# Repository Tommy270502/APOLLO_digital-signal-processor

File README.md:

# APOLLO Digital Signal Processor

APOLLO is a USB-powered STM32F401 digital signal-processing board and firmware
case study. The repository combines KiCad hardware design, STM32CubeIDE
firmware, external analog and memory devices, host-side tests for reusable C
logic, and validation notes for hardware-dependent behavior.

## What This Demonstrates

- STM32F401 firmware architecture with CubeMX-generated code kept separate from
  hand-written application logic.
- USB CDC command and telemetry interface for live DSP configuration.
- Two-channel analog input support, external I2C DAC output, and SPI SRAM
  circular sample logging.
- Embedded-friendly DSP filters with fixed buffers and parameter validation.
- Clear distinction between implemented, host-tested, and hardware-validation
  required features.

## System Overview

```mermaid
flowchart LR
    Host["PC serial monitor"] <-- "USB CDC" --> USB["USB-C + ESD"]
    USB --> MCU["STM32F401RBTx\n84 MHz Cortex-M4F"]
    AIN["AIN0 / AIN1"] --> Analog["MCP602 analog conditioning"]
    Analog --> ADC["ADC1 CH0 / CH1"]
    ADC --> MCU
    MCU -- "I2C1 PB6/PB7" --> DAC["MCP4725-family\n12-bit I2C DAC"]
    DAC --> AOUT["Analog output"]
    MCU -- "SPI1 PA5/PA6/PA7" --> SRAM["23K256\n32 KiB SPI SRAM"]
    MCU -- "SPI1 + SD_nCS" --> SD["microSD socket\nFatFs CSV logging"]
    MCU --> SWD["SWD debug"]
    MCU --> UART["USART1 header"]
```

## Firmware Architecture

```mermaid
flowchart TD
    Main["main.c\nHAL + CubeMX init"] --> App["app/apollo_app"]
    App --> ADC["platform/apollo_adc\nbounded polling"]
    App --> USB["platform/apollo_usb_cdc\nRX line buffer + TX wrapper"]
    App --> Chain["app/apollo_signal_chain"]
    Chain --> DSP["dsp/dsp_filters"]
    App --> DAC["drivers/dac_driver"]
    App --> Store["app/apollo_storage"]
    Store --> SRAM["drivers/sram_23k256"]
    App --> Tel["app/apollo_telemetry"]
    App --> Diag["app/apollo_diagnostics"]
    App --> CLI["app/apollo_cli"]
```

`main.c` now performs HAL initialization, CubeMX peripheral initialization, and
then calls `apollo_app_init()` and `apollo_app_task()`. Application behavior is
kept under `Software/Apollo - DSP/Core/Inc/*` and
`Software/Apollo - DSP/Core/Src/*`.

## Signal Pipeline

```mermaid
flowchart LR
    Source{"Source"} -->|ADC CH0/CH1| Raw["raw ADC"]
    Source -->|demo mode| Raw
    Raw --> Cal["offset/gain calibration"]
    Cal --> Filter["runtime DSP filter"]
    Filter --> Clamp["DAC saturation handling"]
    Clamp --> DAC["I2C DAC write"]
    Filter --> Telemetry["USB CDC telemetry"]
    Clamp --> Log["SPI SRAM circular log"]
    Raw --> Diagnostics["min/max/mean/errors"]
```

Default firmware behavior preserves the original demo path: ADC channel 0 is
sampled, a 1 kHz first-order low-pass filter is applied, the result is written
to the external DAC, telemetry is streamed over USB CDC, and compact sample
records are written to external SRAM when the SRAM self-test passes.

## USB Commands

Commands are sent over the USB CDC virtual COM port with newline termination.

| Command | Purpose |
| --- | --- |
| `help` | Print command summary. |
| `status` | Print sample count, channel, filter, demo, calibration, storage, and error counters. |
| `filter bypass` | Disable filtering. |
| `filter lowpass <hz>` | First-order low-pass IIR. |
| `filter highpass <hz>` | First-order high-pass IIR. |
| `filter ema <alpha>` | Exponential moving average, `0 < alpha <= 1`. |
| `filter average <n>` | Moving average, up to 16 samples. |
| `filter median <n>` | Median filter, up to 9 samples. |
| `input 0` / `input 1` | Select ADC channel 0 or 1. |
| `demo off\|sine\|step\|impulse` | Use real ADC input or synthetic samples. |
| `telemetry on\|off` | Enable or disable periodic telemetry frames. |
| `calibrate clear` | Restore unity ADC/DAC scaling. |
| `calibrate adc <gain> <offset>` | Set ADC input calibration (gain 0.01-100, offset +/-4095). |
| `calibrate dac <gain> <offset>` | Set DAC output calibration (gain 0.01-100, offset +/-4095). |

## Telemetry

Sample frames use this CSV format:

```text
T,timestamp_ms,sequence,channel,raw_adc,filtered,dac_code,filter,flags
```

Example:

```text
T,1200,57,0,1820,1784.42,1784,lowpass,0x00000000
```

Flags report clipping, demo source, filter errors, ADC errors, DAC errors, and
SRAM logging errors.

## Repository Layout

| Path | Purpose |
| --- | --- |
| `Apollo - DSP.kicad_pro` | Main KiCad project. |
| `Apollo - DSP.kicad_sch`, `Analog.kicad_sch`, `DSP.kicad_sch` | Hardware schematics. |
| `Apollo - DSP.kicad_pcb` | PCB layout. |
| `Gerber/` | Fabrication outputs. |
| `pictures/` | Board images. |
| `datasheets/` | Local component datasheets. |
| `Software/Apollo - DSP/` | STM32CubeIDE firmware project. |
| `tests/host/` | Host-buildable tests for pure C logic. |
| `docs/` | Technical documentation and validation notes. |

See [REPOSITORY_STRUCTURE.md](REPOSITORY_STRUCTURE.md) for more detail.

## Build And Flash

1. Open STM32CubeIDE.
2. Import `Software/Apollo - DSP/` as an existing STM32CubeIDE project.
3. Build the Debug or Release configuration.
4. Flash/debug over the SWD header using an ST-LINK compatible probe.
5. Open the USB CDC virtual COM port with a serial terminal.
6. Send `help`, `status`, or `demo sine` to verify the command path.

Generated `Debug/` and `Release/` folders are intentionally not tracked.
STM32CubeIDE regenerates them locally.

## Host Tests

Host tests cover pure logic that does not require STM32 HAL or board hardware:

```sh
make -C tests/host test
```

The tests exercise DSP filter behavior, command parsing, telemetry formatting,
diagnostics, calibration/clipping math, and signal-chain demo paths.

## Validation Status

- Host tests pass on Windows 11 / MSYS2 / GCC 15.2.0 (2026-05-27).
- Firmware Debug and Release builds pass with 0 errors (STM32CubeIDE 2.0.0,
  arm-none-eabi-gcc 14.3.1, 2026-05-27).
- Hardware-dependent behavior requires board validation:
  ADC channel accuracy, DAC output voltage, SRAM SPI timing, and USB behavior
  under sustained traffic.
- microSD logging writes CSV through FatFs over an SPI block driver; the
  logic is covered by host tests but has not been exercised on a card yet
  until a real SPI block-device and filesystem implementation is added.

See [docs/validation.md](docs/validation.md) for the full validation checklist.

## Engineering Highlights

- CubeMX-generated code is preserved and hand-written application code is moved
  into reviewable modules.
- Peripheral failures no longer force infinite retry loops in application code.
- Runtime filter selection and demo sources make the board demonstrable without
  external analog equipment.
- Documentation states validation limits instead of claiming untested hardware
  support.

## Future Work

- Move ADC acquisition to timer-triggered DMA with overrun accounting.
- Validate microSD logging on hardware and record the observed results.
- Add fixture-based hardware tests for DAC linearity, ADC channel calibration,
  SRAM retention, and USB throughput.
- Add optional firmware CI if a reproducible STM32 toolchain image is adopted.

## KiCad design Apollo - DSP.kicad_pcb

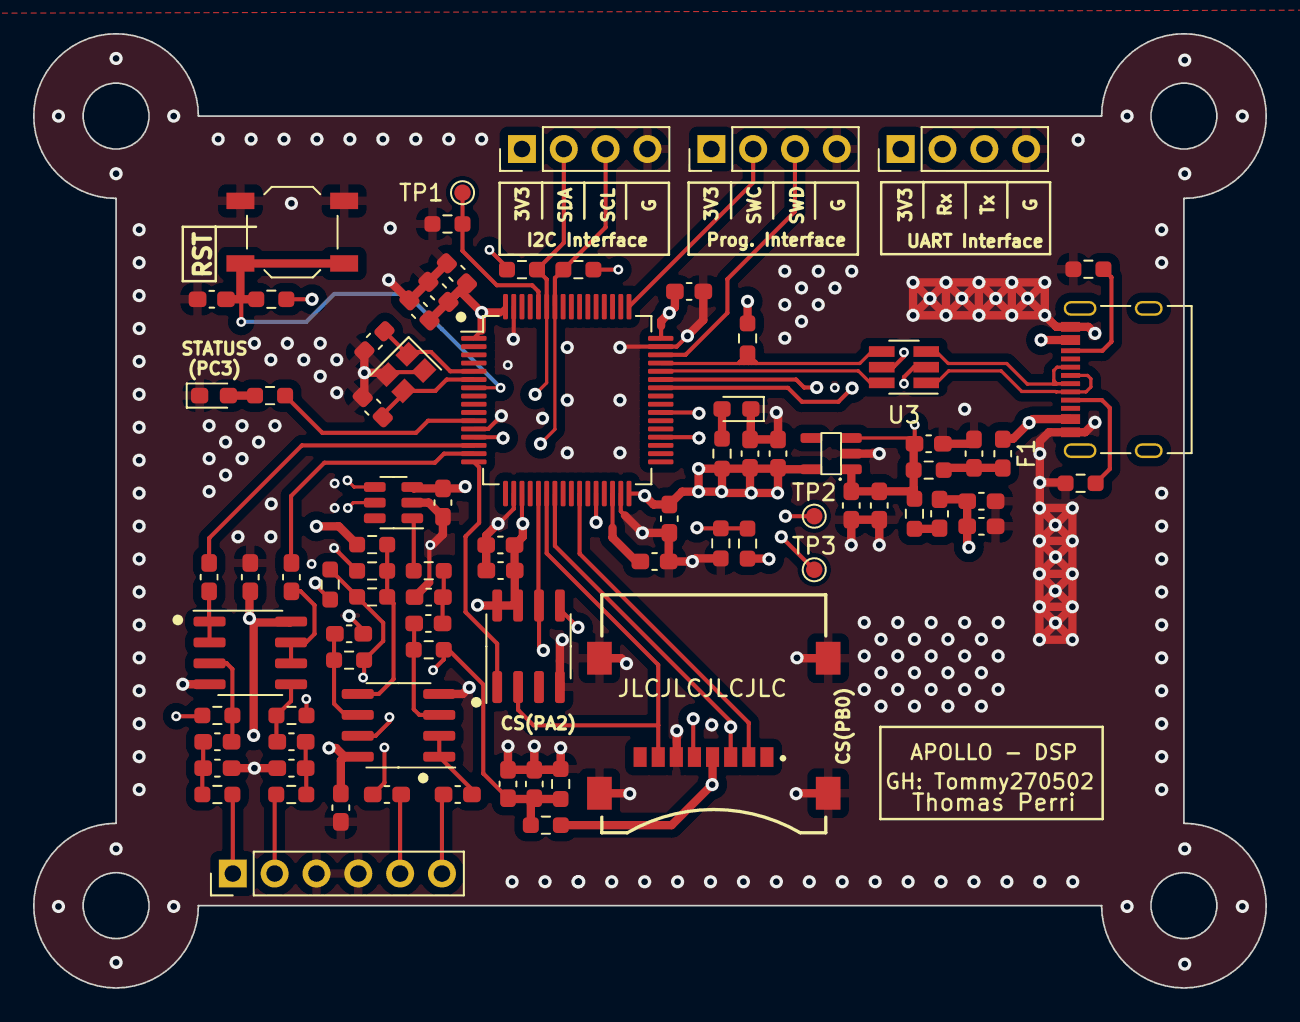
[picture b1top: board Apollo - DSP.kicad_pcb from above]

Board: 4 copper layers, 74.9 x 58.0 mm, 83 parts (0 on the bottom side), 56 nets.

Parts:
C1, C2, C3, C5, C8, C13, C14, C20, C23: 10u; C_0603_1608Metric_Pad1.08x0.95mm_HandSolder
C4, C6, C15, C16, C17, C18, C19, C21, C26, C29, C30, C31, C32, C34, C36, C37, C39, C40, C41, C42: 100n; C_0603_1608Metric_Pad1.08x0.95mm_HandSolder
C7: 220u; C_0603_1608Metric_Pad1.08x0.95mm_HandSolder
C24, C25: 10p; C_0603_1608Metric_Pad1.08x0.95mm_HandSolder
C33, C35, C38: 1n; C_0603_1608Metric_Pad1.08x0.95mm_HandSolder
D1: Red; LED_0603_1608Metric_Pad1.05x0.95mm_HandSolder
D2: Green; LED_0603_1608Metric_Pad1.05x0.95mm_HandSolder
F1: 500mA; Fuse_0603_1608Metric_Pad1.05x0.95mm_HandSolder
FB1: 100R@100MHz; R_0603_1608Metric_Pad0.98x0.95mm_HandSolder
J1: USB_C_Receptacle_USB2.0; USB_C_Receptacle_Palconn_UTC16-G
J2, J3, J6: Conn_01x04; PinHeader_1x04_P2.54mm_Vertical
J4: MEM2067-02-180-00-A_REVB; GCT_MEM2067-02-180-00-A_REVB
J5: Conn_01x06; PinHeader_1x06_P2.54mm_Vertical
L1: 8u8; L_0603_1608Metric_Pad1.05x0.95mm_HandSolder
R1, R8: 1k; R_0603_1608Metric_Pad0.98x0.95mm_HandSolder
R2, R3: 5.1k; R_0603_1608Metric_Pad0.98x0.95mm_HandSolder
R4, R5, R9, R10, R16, R18, R19, R21: 5k1; R_0603_1608Metric_Pad0.98x0.95mm_HandSolder
R6, R7, R22, R23: 10k; R_0603_1608Metric_Pad0.98x0.95mm_HandSolder
R11, R12, R15: 1M; R_0603_1608Metric_Pad0.98x0.95mm_HandSolder
R13: 1.5k; R_0603_1608Metric_Pad0.98x0.95mm_HandSolder
R13#2, R14, R17, R20: 160R; R_0603_1608Metric_Pad0.98x0.95mm_HandSolder
R24: 10R; R_0603_1608Metric_Pad0.98x0.95mm_HandSolder
RESET1: RST; SW_SPST_TL3342
TP1, TP2, TP3: TestPoint; TestPoint_Pad_D1.0mm
U1: NCP115ASN330T2G
U3: USBLC6-2SC6; SOT-23-6_Handsoldering
U4: STM32F401RBTx; LQFP-64_10x10mm_P0.5mm
U5: 23K256; SOIC-8_3.9x4.9mm_P1.27mm
U6: MCP4725xxx-xCH; SOT-23-6
U7, U8: MCP602; SOIC-8_3.9x4.9mm_P1.27mm
Y1: 16MHz; Crystal_SMD_2520-4Pin_2.5x2.0mm

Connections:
3.3V: C5.1, C6.1, C15.1, C16.1, C17.1, C18.1, C19.1, C20.1, C26.1, C29.2, J2.1, J3.1, J4.4 (VDD), J6.1, R1.2, R4.2, R6.1, R9.2, R10.2, R13.1, R23.1, U1.5 (out), U4.1 (VBAT), U4.13 (VREF+), U4.19 (VDD), U4.32 (VDD), U4.48 (VDD), U4.64 (VDD), U5.7 (nHLD), U5.8 (VCC), U6.3 (VDD)
+5V: C2.1, C3.1, C4.1, FB1.2, R24.1, U1.1 (in), U1.3 (EN), U3.5
+5VA: C7.1, C8.1, C39.2, C42.2, L1.2, R21.1, U7.8 (V+), U8.8 (V+)
/Analog/CH0_+: C30.2, R11.1, U7.3 (+)
/Analog/CH0_LPF: C30.1, C33.2, R13#2.1
/Analog/CH0_OP_OUT: C32.1, U7.1, U7.2 (-)
/Analog/CH1_+: C36.2, R15.1, U7.5 (+)
/Analog/CH1_LPF: C36.1, C38.2, R17.1
/Analog/CH1_OP_OUT: C37.1, U7.6 (-), U7.7
/POW: F1.1, J1.A4 (VBUS), J1.A9 (VBUS), J1.B4 (VBUS), J1.B9 (VBUS)
ADC_CH0_IN: C32.2, U4.14 (PA0)
ADC_CH1_IN: C37.2, U4.15 (PA1)
AIN0: J5.1, R13#2.2
AIN1: J5.2, R17.2
AOUT: C34.2, J5.6
BOOT0: R7.1, TP1.1, U4.60 (BOOT0)
BOOT1: R22.1, R23.2, U4.28 (PB2)
DAC_OUT: R14.2, U6.1 (VOUT)
GND: C1.2, C2.2, C3.2, C4.2, C5.2, C6.2, C7.2, C8.2, C13.2, C14.2, C15.2, C16.2, C17.2, C18.2, C19.2, C20.2, C21.2, C23.2, C24.2, C25.2, C26.2, C29.1, C33.1, C35.1, C38.1, C39.1, C41.1, C42.1, D1.1 (K), D2.1 (K), J1.A1 (GND), J1.A12 (GND), J1.B1 (GND), J1.B12 (GND), J2.4, J3.4, J4.6 (VSS), J4.9 (SHIELD), J4.10 (SHIELD), J4.11 (SHIELD), J4.12 (SHIELD), J5.3, J5.4, J6.4, R2.2, R3.2, R5.2, R7.2, R18.2, R22.2, RESET1.1, U1.2 (GND), U3.2, U4.12 (VSSA), U4.18 (VSS), U4.31 (VSS), U4.47 (VSS), U4.63 (VSS), U5.4 (GND), U6.2 (VSS), U7.4 (V-), U8.4 (V-), Y1.2, Y1.4
MISO: J4.7 (DAT0), U4.22 (PA6), U5.2 (SO)
MOSI: J4.3 (CMD), U4.23 (PA7), U5.5 (SI)
NRST: C21.1, R6.2, RESET1.2, U4.7 (NRST)
unnamed: C31.1, C35.2, R14.1
unnamed: C40.1, R20.1
unnamed: D1.2 (A), R1.1
unnamed: D2.2 (A), R8.2
unnamed: J1.A5 (CC1), R2.1
unnamed: J1.B5 (CC2), R3.1
unnamed: L1.1, R24.2
unnamed: R16.1, R19.1, R20.2, U8.7
unnamed: TP3.1, U4.36 (PB15)
unnamed: R8.1, U4.11 (PC3)
unnamed: TP2.1, U4.39 (PC8)
unnamed: C23.1, U4.30 (VCAP1)
unnamed: C31.2, R12.1, U8.3 (+)
unnamed: C34.1, U8.1, U8.2 (-)
unnamed: R16.2, R18.1, R21.2, U8.5 (+)
unnamed: C41.2, R19.2, U8.6 (-)
OSC: C40.2, J5.5
RAM_nCS: U4.16 (PA2), U5.1 (nCS)
Rx: J3.2, U4.43 (PA10)
SCK: J4.5 (CLK), U4.21 (PA5), U5.6 (SCK)
SCL: J6.3, R9.1, U4.58 (PB6), U6.5 (SCL)
SDA: J6.2, R10.1, U4.59 (PB7), U6.4 (SDA)
SD_nCS: J4.2 (CD/DAT3), U4.26 (PB0)
SWCLK: J2.2, U4.49 (PA14)
SWDIO: J2.3, U4.46 (PA13)
Tx: J3.3, U4.42 (PA9)
USB_CONN_+: J1.A6 (D+), J1.B6 (D+), U3.3
USB_CONN_-: J1.A7 (D-), J1.B7 (D-), U3.1
USB_D+: R13.2, U3.4, U4.45 (PA12)
USB_D-: U3.6, U4.44 (PA11)
VAA: C13.1, C14.1, R4.1, R5.1, R11.2, R12.2, R15.2
VBUS: C1.1, F1.2, FB1.1
X1: C24.1, U4.5 (PH0), Y1.1
X2: C25.1, U4.6 (PH1), Y1.3

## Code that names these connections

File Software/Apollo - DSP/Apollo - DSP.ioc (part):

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Mcu.Name=STM32F401R(B-C)Tx
Mcu.Package=LQFP64
Mcu.UserName=STM32F401RBTx
PA0-WKUP.Signal=ADCx_IN0
PA1.Signal=ADCx_IN1
PA10.Mode=Asynchronous
PA10.Signal=USART1_RX
PA11.Mode=Device_Only
PA11.Signal=USB_OTG_FS_DM
PA12.Mode=Device_Only
PA12.Signal=USB_OTG_FS_DP
PA13.Mode=Serial_Wire
PA13.Signal=SYS_JTMS-SWDIO
PA14.Mode=Serial_Wire
PA14.Signal=SYS_JTCK-SWCLK
PA5.Mode=Full_Duplex_Master
PA5.Signal=SPI1_SCK
PA6.Mode=Full_Duplex_Master
PA6.Signal=SPI1_MISO
PA7.Mode=Full_Duplex_Master
PA7.Signal=SPI1_MOSI
PA9.Mode=Asynchronous
PA9.Signal=USART1_TX
PB6.Mode=I2C
PB6.Signal=I2C1_SCL
PB7.Mode=I2C
PB7.Signal=I2C1_SDA
PH0\ -\ OSC_IN.Mode=HSE-External-Oscillator
PH0\ -\ OSC_IN.Signal=RCC_OSC_IN
PH1\ -\ OSC_OUT.Mode=HSE-External-Oscillator
PH1\ -\ OSC_OUT.Signal=RCC_OSC_OUT
RCC.HSE_VALUE=16000000
RCC.SYSCLKFreq_VALUE=84000000
RCC.SYSCLKSource=RCC_SYSCLKSOURCE_PLLCLK
board=custom

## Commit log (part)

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2023-01-27 added a pinheader for analog signal in
2023-01-27 Added polygons
2023-01-27 added pics
2023-02-03 had to change mcu since the stm32f103 does not have an FPU -> too slow for DSP applications
2023-02-03 completed schematic and layout with new mcu, also added an SPI connector
2023-02-03 forgot the cs pins
2023-02-03 added silkscreen pin assignment of cs pins
2023-02-03 more silkscreen stuff
2023-02-04 moved decoupling caps closer to dsp
2023-02-04 added more silkscreen lables
2023-02-04 hardware completed
2023-02-04 added some relevant datasheets
2023-02-04 repoured all polygons
2023-02-05 wrote some code to read out an adc input filter it and send it out through usb
2023-02-16 modified usbc footprint
2023-02-16 trying to generate bom with kibom
2023-02-16 changed footprint of caps
2023-02-18 grounded mounting holes gnd top layer polygon and cool looking gnd strips on analog side
2023-02-18 minor modifications with refs and new pictures
2023-02-18 fixed mounting hole size from 6mm diam to 3mm diam
2023-02-18 own foorprint for LDO
2023-02-18 generated gerber files
2023-02-18 replaced 741 opamp for lm358 due to cost reasons
2023-02-18 need to add 3d model for power regulator
2023-02-18 added 3d model and updated pics
2023-02-18 added jlcpcb ordernumber location
2023-02-18 regenerated gerbers
2023-02-18 finished
2023-02-24 tiedied usb differential pair routing
2023-02-24 new gerber
2023-03-29 added boot and reset button
2023-03-29 fixed usb differential routing -> no vias
2023-03-29 added 3d model for sd card
2023-04-12 smaller pcb removed ram unneccessary
2023-04-12 smaller mounting holes improved usb routing
2023-04-13 removed solver mask from mounting holes and grounded it
2023-04-13 added pcb edge vias and grounded them (basically just esthethically pleasing but certaintly helps to shield analog side)
2023-04-14 start organising connectors
2023-04-14 added feature in the Lowpass init function to make sure the cutoff frequency is at least two times than the sample frequency
2023-05-02 fancy copper on edges
2023-05-07 moved analog power farther away from digital Power, removed SPI and I2C Interface since it was not needed in the V1
2023-05-07 cleaned up the whole board
2023-05-09 made analog circuitry a bit more compact moved whole board
2023-05-09 cleanup
2023-05-09 finished?
2023-05-15 added sram chip again, might come in handy for mor complex calculations
2023-05-15 made 3d pics
2023-05-18 updated pics
2023-05-18 added DAC and an onboard fixed oscilltor to quickly test the DSP
2023-05-18 silkscreen stuff
2023-05-22 added teardrops to increase yield&quality, also tuned usb data line skew
2023-05-22 repoured polygons
2023-05-23 started writing drivers for the DAC and RAM IC's
2023-05-26 implementing test ram function
2023-05-27 testram function finished
2023-05-27 writing code to test out adc, usb and ram
2023-05-28 writing code for the DAC
2023-05-30 completed driver code for DAC, ready for testing when PCBs are assembled
2023-05-30 created .c and .h files for SDCARD drivers
2023-06-07 fixed bootloader setting to SWD, removed boot button.
2023-08-31 some changes
2023-08-31 modifications for rev 3
2023-10-03 ready for order
2023-10-05 checking for possible mistakes
2023-10-18 FIXED ADCVOLTAGE PIN
2024-02-19 refreshing design
2026-05-21 better readme + architecture
2026-05-21 refactor
2026-05-26 Add Claude local settings
2026-05-26 Remove AI assistant files from repo
2026-05-26 Track host test Makefile
